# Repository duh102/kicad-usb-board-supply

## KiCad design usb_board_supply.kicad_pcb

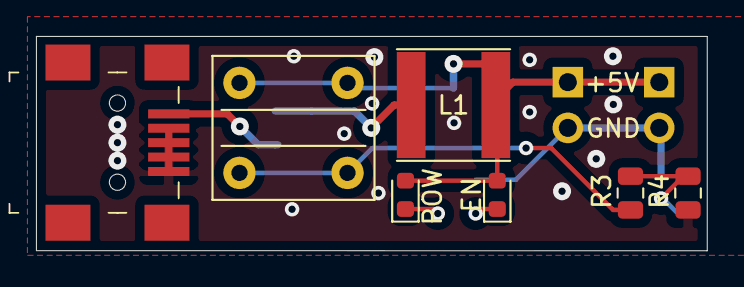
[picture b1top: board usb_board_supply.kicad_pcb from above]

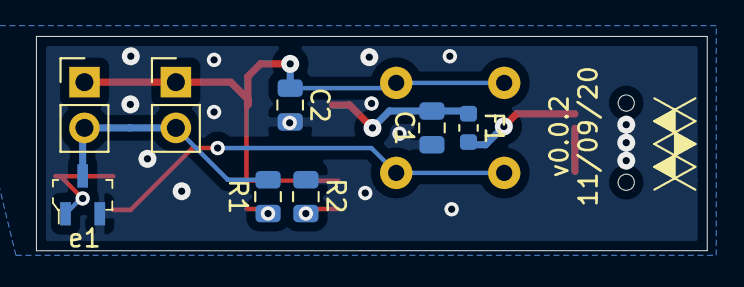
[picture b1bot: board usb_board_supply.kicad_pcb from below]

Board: 2 copper layers, 37.3 x 11.9 mm, 15 parts (8 on the bottom side), 9 nets.

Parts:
C1, C2: 1uF; C_0805_2012Metric
EN: EN; LED_0603_1608Metric
F1: 2A; Fuse_0603_1608Metric
J1: USB_B_Micro; USB_Mini_B_Female_690-005-299-043
J2, J3: Conn_01x02; PinHeader_1x02_P2.54mm_Vertical
L1: 33uH 1.1A; L_Taiyo-Yuden_NR-60xx
POW: POW; LED_0603_1608Metric
R1, R2, R3: 10kR; R_0805_2012Metric
R4: 1MR; R_0805_2012Metric
SW1: ON/OFF; SW_CuK_PVA1_9.8x9.2mm
e1: BSS138; SOT-23-3

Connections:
GND: C1.2, C2.2, J1.2, J1.3, J1.4, J1.5, R2.2, R4.2, e1.2
unnamed: C1.1, F1.1, L1.1
unnamed: EN.1, R1.1
unnamed: POW.1, R2.1
unnamed: R3.1, SW1.2, SW1.4
unnamed: R3.2, R4.1, e1.1
V0UT: J2.2, J3.2, R1.2, e1.3
V+: F1.2, J1.1
VFILT: C2.1, EN.2, J2.1, J3.1, L1.2, POW.2, SW1.1, SW1.3

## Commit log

2020-12-09 Update to use mosfet instead of switch
